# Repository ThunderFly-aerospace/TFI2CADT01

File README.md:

# TFI2CADT01 - I²C address translator

TFI2CADT01 is an I2C device address changer. This function allows you to connect multiple I2C devices with the same address to one master device on the same bus.

That is a common problem in case multiple I2C sensors with the same address (or a limited number of addresses) need to be connected to one I2C master. The purpose of this module is to change the address with which the I2C master calls to the address of the target I2C (slave) device.
The module is based on [LTC4317](https://www.analog.com/media/en/technical-documentation/data-sheets/4317fa.pdf) I2C address translator IC.
The module is designed and optimized for use on Pixhawk-compatible drones, especially UAVs. The design of the module is compatible with the [dronecode connectors standard](https://github.com/pixhawk/Pixhawk-Standards/blob/master/DS-009%20Pixhawk%20Connector%20Standard.pdf).

## Where to get it?

ThunderFly I2C address translator is commercially available from [ThunderFly s.r.o.](https://www.thunderfly.cz/), write an email to info@thunderfly.cz or shop at [Tindie store](https://www.tindie.com/products/thunderfly/tfi2cadt01-i2c-address-translator/).

## Translation function

The called address of the slave device is translated by a logical operation [XOR](https://en.wikipedia.org/wiki/Bitwise_operation#XOR) with the address bits configured in the TFI2CADT01 module. Each TFI2CADT01 port has a different default address. The address of each port can be changed independently by soldering solder jumpers JP1 and JP2.

NOTE: The TFI2CADT01 is not an I2C buffer, therefore the quality of input bits affects its function, and also corrupted data on input are propagated on the output. The address translator does XOR with the input address clocked in. To avoid related issues with bus data integrity we strongly recommend using ThunderFly's [TFCABI2C cables](https://github.com/ThunderFly-aerospace/TFCAB01) which minimizes SDA/SCL crosstalks. In some cases, where the I2C network has a significant length or number of nodes the use of [TFI2CEXT01](https://github.com/ThunderFly-aerospace/TFI2CEXT01), that is I2C extender with buffer function. 

## Configuration

The default address translation is listed in the following table.

| Port | Solder jumper | XOR value (in hex) | XOR value in binary form |
|---|---|---|---|
| 1 | Disconnected (default) | 0x08 | 0b0001000 |
| 1 | Soldered     | 0x0f | 0b0001111 |
| 2 | Disconnected (default) | 0x78 | 0b1111000 |
| 2 | Soldered     | 0x7f | 0b1111111 |

The connectors on the top side and the unpopulated connector on the bottom side are identical. There is no address difference between them. That should be used to split the bus to other sensors.

### Determining the new address of the I2C device

The new device address which should be called by the master could be calculated by doing XOR with the TFI2CADT01 port address and original device address.  The result is the new device address. You can use an [online calculator](https://xor.pw/) to do that. Another approach is determining the new address heuristically by use of the `i2cdetect` command or similar. 

## Example of usage

The TFI2CADT01 could be used with a wide variety of ThunderFly or Pixhawk I²C sensors, here are a few examples.

### Tachometer (RPM) sensors

The TFI2CADT01 could be easily used for the connection of multiple [TFRPM01 tachometer](https://github.com/ThunderFly-aerospace/TFRPM01) sensors, which is especially useful for multi-rotor airframes.

### Redundant airspeed sensors

The TFI2CADT01 could also fix troubles with the connection of multiple [TFSLOT01 airspeed sensors](https://github.com/ThunderFly-aerospace/TFSLOT01) to one bus. It could be used even for other I2C-based airspeed sensors. That could increase the redundancy, in situations where a failure of the sensor is more probable than failure of the bus itself.

### Temperature and hygrometer sensors

For example the [TFHT01](https://github.com/ThunderFly-aerospace/TFHT01) connected by use of TFI2CADT01 allows measuring of temperature and humidity by multiple airframe locations at once.

## FAQ

### How I can change the I2C addresses used in the Pixhawk to the ones translated by the TFI2CADT01?

The translated addresses might not be recognized by default in the PX4 (that is usually experienced in the case of the SDP3x sensor driver).
One approach to solve that is to create a configuration file named `config.txt` on the SD card as is documented in the [PX4 documentation](https://docs.px4.io/main/en/concept/system_startup.html#replacing-the-system-startup). In this file, you can specify the start commands for the driver of the translated sensors.

Here's an example of the content of the `/etc/config.txt` on the SD card:

```
sdp3x_airspeed start -X -a <translated_address_a>
sdp3x_airspeed start -X -a <translated_address_b>
```

Replace `<translated_address_a>` and `<translated_address_b>` with the actual translated I2C addresses of your sensors. Addresses could be obtained by calculating XOR with the original address. Or it can be obtained with the `i2cdetect` command.

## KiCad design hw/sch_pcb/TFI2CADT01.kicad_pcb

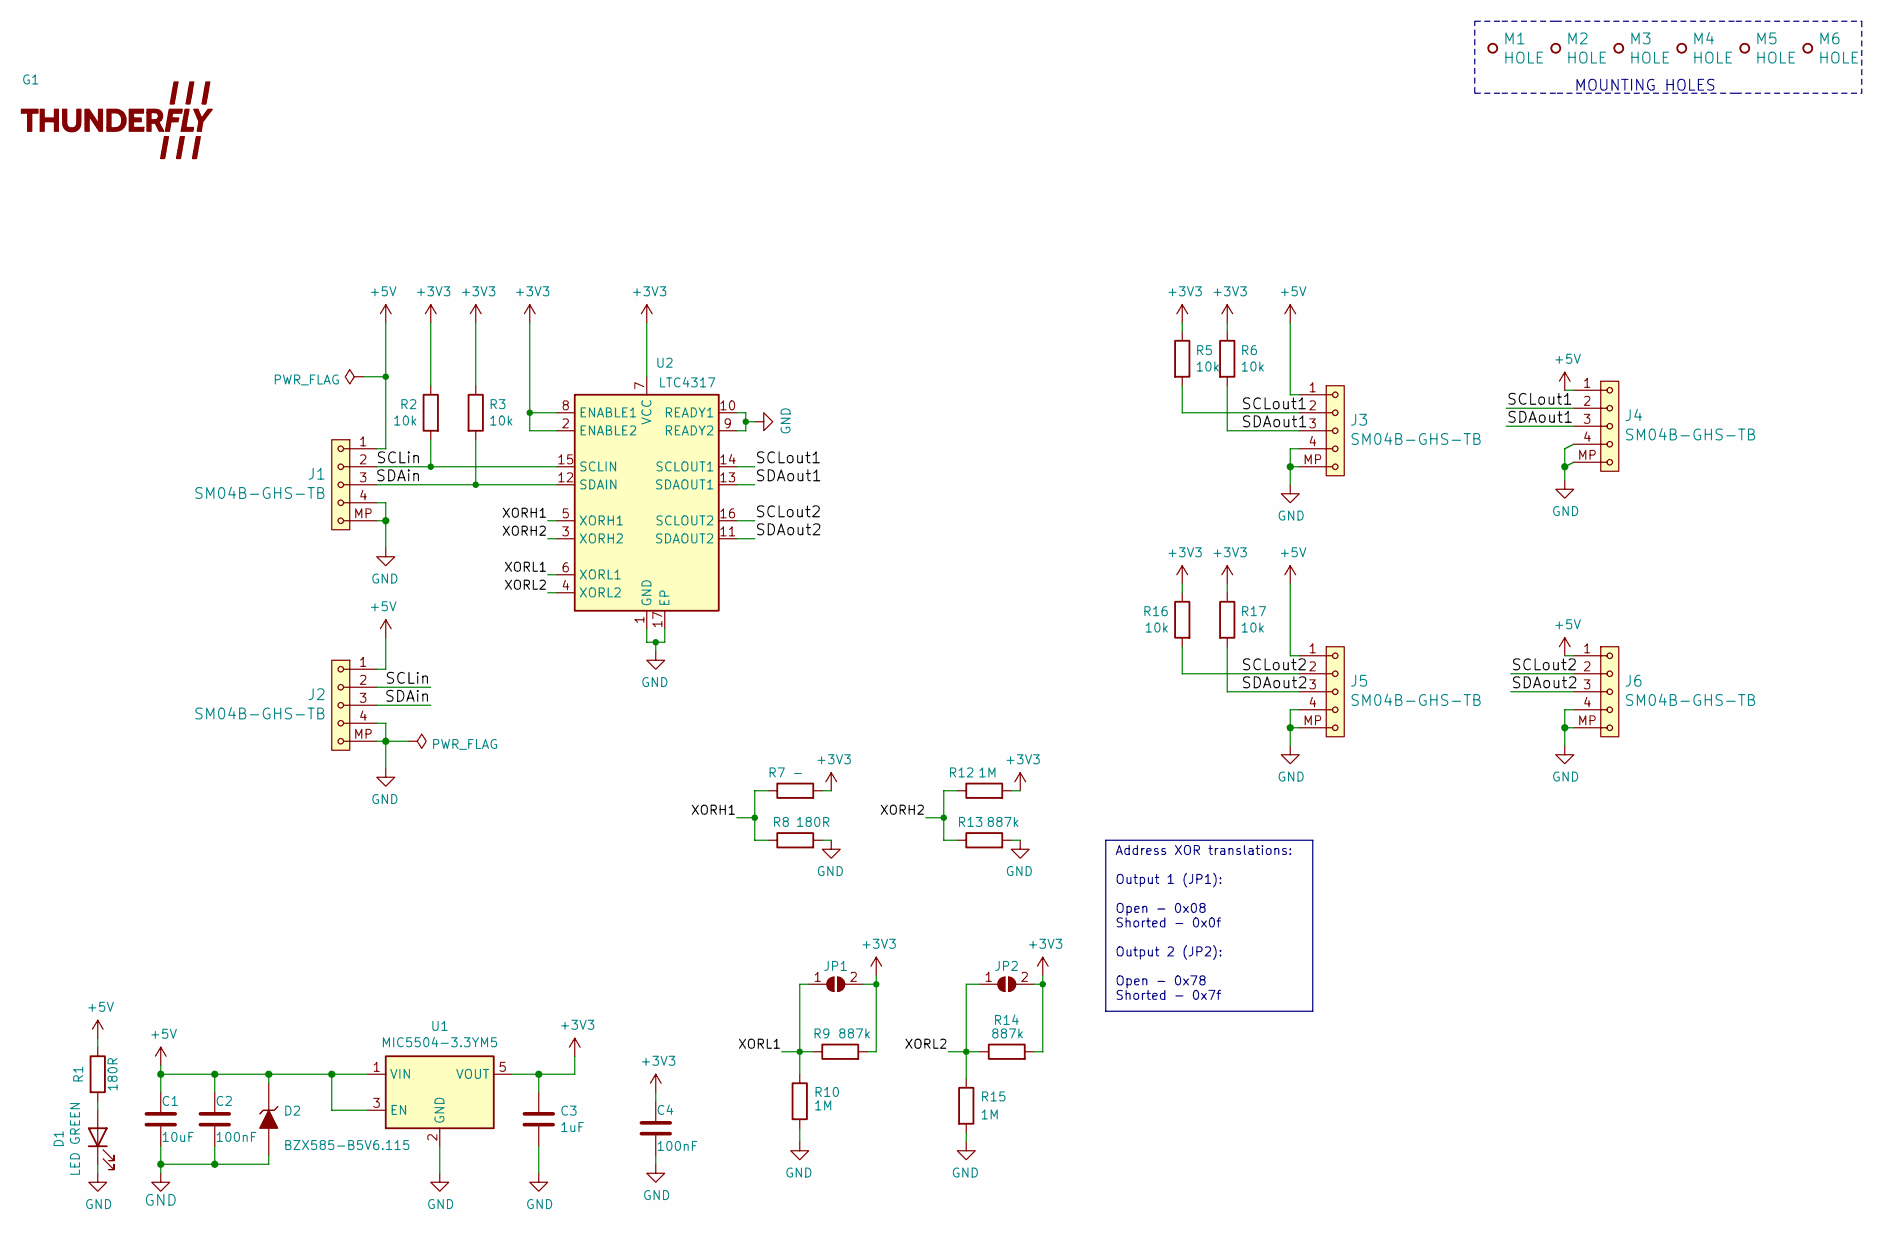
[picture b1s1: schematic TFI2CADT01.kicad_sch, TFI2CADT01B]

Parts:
C1: 10uF; C_0805_2012Metric
C2, C4: 100nF; C_0603_1608Metric
C3: 1uF; C_0603_1608Metric
D1: LED GREEN; LED_0603_1608Metric
D2: BZX585-B5V6.115; D_SOD-523
G1: LOGO; TF 10x4,7
J1, J2, J3, J4, J5, J6: SM04B-GHS-TB; JST_GH_SM04B-GHS-TB_1x04-1MP_P1.25mm_Horizontal
JP1, JP2: SolderJumper_2_Open; SolderJumper-2_P1.3mm_Open_RoundedPad1.0x1.5mm
M1, M2, M3, M4, M5, M6: HOLE; dira_3mm
R1, R8: 180R; R_0603_1608Metric
R2, R3, R5, R6, R16, R17: 10k; R_0603_1608Metric
R7: -; R_0603_1608Metric
R9, R13, R14: 887k; R_0603_1608Metric
R10, R12, R15: 1M; R_0603_1608Metric
U1: MIC5504-3.3YM5; SOT-23-5
U2: LTC4317; DFN-16-1EP_3x5mm_P0.5mm_EP1.66x4.4mm

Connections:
+3V3: C3.1, C4.1, JP1.2 (B), JP2.2 (B), R2.1, R3.1, R5.1, R6.1, R7.2, R9.2, R12.2, R14.2, R16.1, R17.1, U1.5 (VOUT), U2.2 (ENABLE2), U2.7 (VCC), U2.8 (ENABLE1)
+5V: C1.1, C2.1, D2.1 (K), J1.1, J2.1, J3.1, J4.1, J5.1, J6.1, R1.1, U1.1 (VIN), U1.3 (EN)
/SCLin: J1.2, J2.2, R2.2, U2.15 (SCLIN)
/SCLout1: J3.2, J4.2, R5.2, U2.14 (SCLOUT1)
/SCLout2: J5.2, J6.2, R16.2, U2.16 (SCLOUT2)
/SDAin: J1.3, J2.3, R3.2, U2.12 (SDAIN)
/SDAout1: J3.3, J4.3, R6.2, U2.13 (SDAOUT1)
/SDAout2: J5.3, J6.3, R17.2, U2.11 (SDAOUT2)
/XORH1: R7.1, R8.1, U2.5 (XORH1)
/XORH2: R12.1, R13.1, U2.3 (XORH2)
/XORL1: JP1.1 (A), R9.1, R10.1, U2.6 (XORL1)
/XORL2: JP2.1 (A), R14.1, R15.1, U2.4 (XORL2)
GND: C1.2, C2.2, C3.2, C4.2, D1.1 (K), D2.2 (A), J1.4, J1.MP, J2.4, J2.MP, J3.4, J3.MP, J4.4, J4.MP, J5.4, J5.MP, J6.4, J6.MP, R8.2, R10.2, R13.2, R15.2, U1.2 (GND), U2.1 (GND), U2.9 (READY2), U2.10 (READY1), U2.17 (EP)
unnamed: D1.2 (A), R1.2

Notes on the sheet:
Address XOR translations: Output 1 (JP1): Open - 0x08 Shorted - 0x0f Output 2 (JP2): Open - 0x78 Shorted - 0x7f
MOUNTING HOLES

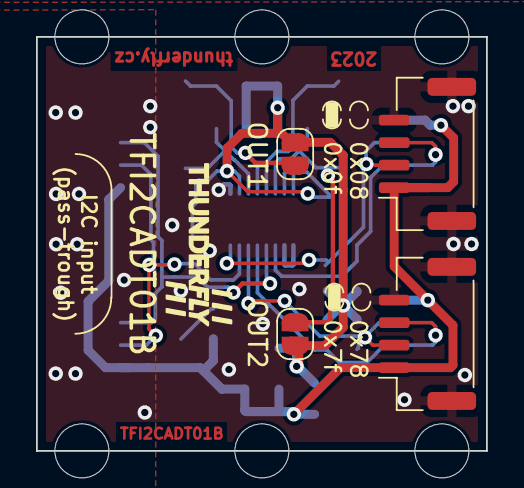
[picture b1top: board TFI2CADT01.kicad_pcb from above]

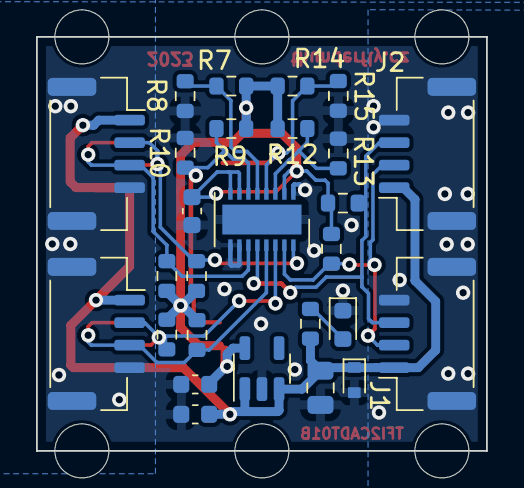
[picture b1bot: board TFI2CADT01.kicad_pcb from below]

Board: 2 copper layers, 25.0 x 23.0 mm, 38 parts (27 on the bottom side), 14 nets.

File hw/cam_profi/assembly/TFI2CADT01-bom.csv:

Row,Description,Part,References,Value,Footprint,Quantity Per PCB,Status,Datasheet,UST_id
1,Unpolarized capacitor,C,C2 C4,100nF,C_0603_1608Metric,2, ,,5c70984812875079b91f8bf2
2,Unpolarized capacitor,C,C3,1uF,C_0603_1608Metric,1, ,,5c70984812875079b91f8bc2
3,Unpolarized capacitor,C,C1,10uF,C_0805_2012Metric,1, ,,5c70984812875079b91f8bbd
4,,D_ZENER,D2,BZX585-B5V6.115,D_SOD-523,1, ,,60879d38128750769ee58e48
5,Light emitting diode,LED,D1,LED GREEN,LED_0603_1608Metric,1, ,,60d582331287500165f859d0
6,,SM04B-GHS-TB,J1 J2 J3 J4 J5 J6,SM04B-GHS-TB,JST_GH_SM04B-GHS-TB_1x04-1MP_P1.25mm_Horizontal,6, ,,5c86273d1287500b4e0280be
7,Resistor,R,R1 R8,180R,R_0603_1608Metric,2, ,,5c70984512875079b91f8957
8,Resistor,R,R2 R3 R5 R6 R16 R17,10k,R_0603_1608Metric,6, ,,5c70984512875079b91f8962
9,Resistor,R,R9 R13 R14,887k,R_0603_1608Metric,3, ,,6272c899dc56076e9a222bfe
10,Resistor,R,R10 R12 R15,1M,R_0603_1608Metric,3, ,,61e030ee2eac0c9aef5c8995
11,Resistor,R,R7,-,R_0603_1608Metric,1, ,,
12,"Dual I2C/SMBus Address-Translator, DFN-16",LTC4317,U2,LTC4317,DFN-16-1EP_3x5mm_P0.5mm_EP1.66x4.4mm,1, ,https://www.analog.com/media/en/technical-documentation/data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,61e031592eac0c9aef5c89ad
13,"300mA Low-dropout Voltage Regulator, Vout 3.3V, Vin up to 5.5V, SOT-23",MIC5504-3.3YM5,U1,MIC5504-3.3YM5,SOT-23-5,1, ,http://ww1.microchip.com/downloads/en/DeviceDoc/MIC550X.pdf,5c7255e81287500b4e112ea2





Project info:
Schematic:,TFI2CADT01
Variant:,default
Revision:,
Date:,2021-04-05
KiCad Version:,7.0.10-7.0.10~ubuntu23.04.1
Statistics:
Component Groups:,13
Component Count:,29
Fitted Components:,29
Number of PCBs:,1
Total Components:,29

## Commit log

2022-01-10 Edit schema
2022-01-11 volba adres rezistory
2022-01-11 anotace soucastek
2022-01-12 Edit PCB
2022-01-12 uprava popisu
2022-01-12 gitignore
2022-01-12 oprava teplotnich profilu
2022-01-12 uprava routingu
2022-01-13 Images
2022-02-02 kompatibilita s verzi 6
2022-02-06 add images
2022-03-15 pridani assets
2022-03-15 uprava submodulu
2022-03-15 rm old submodule
2022-03-15 update layout
2022-03-15 Update submodule to latest
2022-03-15 uprava schema, sablona
2022-03-24 Update Titleblock Move PCB to center of the page Move grid origin to the bottom left corner of the PCB
2022-03-24 Update assets submodule Update KiCAD workflow
2022-03-24 Resolve ERC issues by adding power flags and updating symbols. Update PCB from schematics.
2022-03-29 Removing old and unrelated wrl model.
2022-03-29 update action, clean repo
2022-03-29 Push actions product
2022-03-29 uprava pro actions
2022-03-29 Uprava symbolu
2022-03-30 uprava assets
2022-03-30 Update actions products
2022-03-30 vycisteni repozitare
2022-04-04 Add ERC exclusion to open collector pins.
2022-06-21 Added test file
2023-02-17 testing notebook
2023-05-05 Update tindie.md
    Correct some unclear sentences. Improve clarity.
2023-05-27 Update actions
2023-05-27 save in kicad6
2023-06-20 Update tindie.md
    Add a reference to different firmware specifically.
2023-08-09 Update README.md
    Link to other I2C deices.
2023-09-27 Upravy pred vyrobou
2023-09-27 Edit kicad_outputs.yml
2023-09-27 Edit
2023-10-02 Edit UST_ID
2024-02-12 Aktualizace metadat
2024-02-13 Improve schematics layout run DRC check.
2024-02-13 Backlink to CADLAB.io has been added.
2024-02-13 Update readme and update submodule to kicadv7
2024-02-13 Update tindie.md
    Fix changelog.
2024-02-13 Update tindie.md
    Fix grammar.
2024-02-14 Update README.md
    Add a FAQ section.
2024-02-14 Improve schematics layout.
2024-02-15 Update README.md
    Add a link to TFI2CEXT.
2024-02-21 Translating TESTING.md
2024-02-21 Update TESTING.md
    minor
2024-02-22 Translation TFI2CADT_TEST.ipynb
2024-02-22 Update metadata files
2025-09-26 Update project to KiCADv9.
2025-09-26 Fix title box content.
